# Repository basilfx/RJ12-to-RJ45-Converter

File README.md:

# RJ12-to-RJ45 Converter
A converter for RJ12 to RJ45 for just a very specific use case.

## Introduction
My charge point connects to my Dutch Smart Meter (DSMR), to dynamically adjust
the maximum allowed current. It utillizes the P1 port, which uses a port with a
RJ12 connector. Between the charger and the DSMR, I installed a Cat 5e cable.

Crimping an RJ12 connector onto a Cat 5e cable will not make a durable
connection. I therefore designed this converter and 3D printed an enclosure for
it, just because I can.

I installed a normal RJ45 connector on both ends of the cable, installed two
converters and installed short 'telephone cables' (with RJ11 connectors) to
connect the charge point to the convert, and the DSMR to the converter.

## Contents
* The `3d/` folder contains a 3D-printable design for an enclosure.
* The `pcb/` folder contains the Kicad schema and board design.

## License
The work in this repository is covered by CC BY-NC-SA 4.0. See the `LICENSE.md`
file for more information.

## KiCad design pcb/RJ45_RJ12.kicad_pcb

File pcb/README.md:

# RJ12-to-RJ45 Converter

## Board

## Schema
You can find the schema [here](RJ12_RJ45.pdf).

## BoM
The (interactive) BoM can be found [here](https://basilfx.github.io/RJ12-to-RJ45-Converter/pcb/BoM/ibom.html).

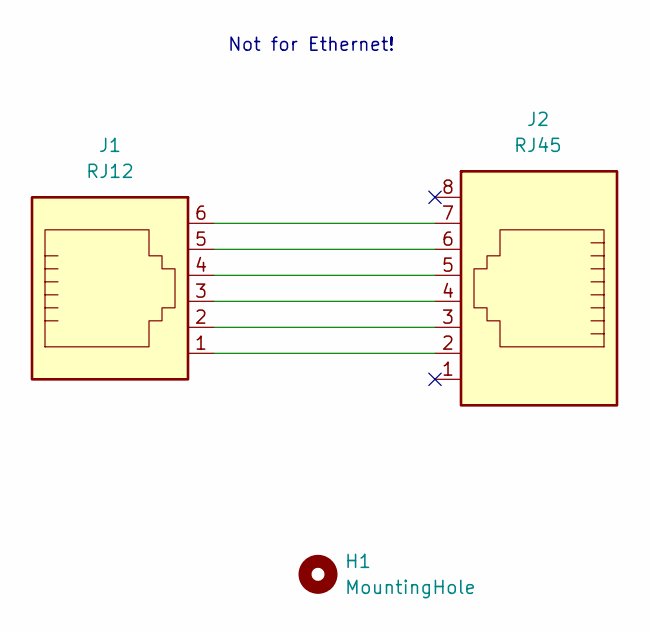
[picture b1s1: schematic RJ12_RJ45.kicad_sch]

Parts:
H1: MountingHole; MountingHole_2.2mm_M2
J1: RJ12; RJ12_Amphenol_54601
J2: RJ45; RJ45_Amphenol_54602-x08_Horizontal

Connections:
unnamed: J1.1, J2.2
unnamed: J1.2, J2.3
unnamed: J1.3, J2.4
unnamed: J1.4, J2.5
unnamed: J1.5, J2.6
unnamed: J1.6, J2.7

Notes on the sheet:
Not for Ethernet!

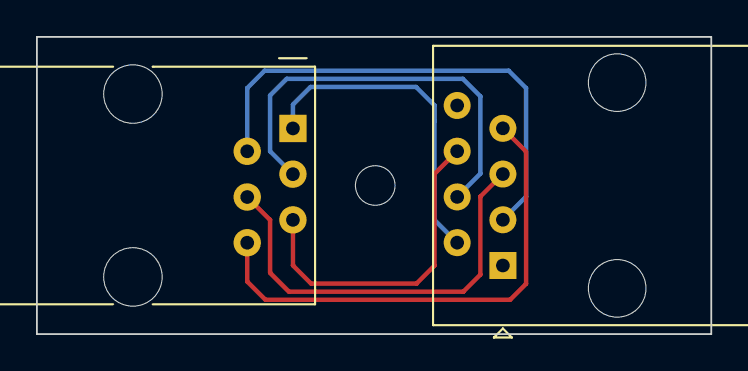
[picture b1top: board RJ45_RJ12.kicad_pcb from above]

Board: 2 copper layers, 37.5 x 16.5 mm, 3 parts (0 on the bottom side), 6 nets.

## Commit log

2022-12-10 Initial import of project
2022-12-10 Fix name of files to fix links
